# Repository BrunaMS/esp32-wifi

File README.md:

# esp32-wifi
In this project I'm using ESP32 with ESP-IDF framework to implement an Wi-Fi connection, allowing to download 500kb files from a device at least 100m away

## Firmware
### Environment
To develop and build this firmware I'm using VSCode and it's extensions. The main extension required to build it is platformIO but others like git extension can be used to help with version control and gitflow. 

### Task routine
To work with different services/threads I chose to use the  

## Hardware
For now, I'm using KiCad 6.0 to create schematics and PCB for this project. During the development was necessary to download components from external sources. These are:
- Example I
- Example II

### Components 
For this project some circuits are necessary, mainly to guarantee battery charging and to protect other modules and the microcontroller from damages.
- BQ - Battery control
- USB Protection circuit
- Crystal
- Voltage regulator
- Wi-Fi antenna performance
- GPIOs

### Microcontroller
The chosen microcontroller for this application was the ESP32-WROOM, developed to work with IoT and wireless in general, making wireless communication protocols easier to develop and use.

### Routing
The general rules for the routing process were:
1. Consider one manufacturer to define the correct pcb specifications (hole size, clearance, board thickness, impedance control, etc)
2. Always consider grounding rules
3. Avoid interference from power lines
4. Avoid keep high-speed signals close to other signals

## TODO 

|Area | Type |Description|
|-----|------|-----------|
|Firmware|Feature|Move device mode selector from kconfig to serial/nvs memory
|Firmware|Feature|Develop some type of interface to be used when it is in receiver mode
|Firmware|Fix| Convert components into real components (submodules in git), making possible the use in other projects
|Firmware|Fix| Organize the different "layers" of the project (e.g. components, common, task, main), creating uncoupled classes/libraries/functions
|Firmware|Docs| Explain function in header (.h file) of each component(brief, params, return) using Doxygen 
|Hardware|Test|Check if with built-in antenna can reach 100m of distance between devices or if its necessary to use another one |

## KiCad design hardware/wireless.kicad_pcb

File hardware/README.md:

# esp32-wifi
In this project I'm using ESP32 with PlatformIO framework to implement an Wi-Fi connection, allowing to download 100mb files from a device at least 100m away

## Firmware
### Environment
To develop and build this firmware I'm using VSCode and it's extensions. The main extension required to build it is platformIO but others like git extension can be used to help with version control and gitflow. 

### Task routine
To work with different services/threads I chose to use the  

## Hardware
For now, I'm using KiCad 6.0 to create schematics and PCB for this project. During the development was necessary to download components from external sources. These are:
- Example I
- Example II

### Components 
For this project some circuits are necessary, mainly to guarantee battery charging and to protect other modules and the microcontroller from damages.
- BQ
- USB Protection circuit
- Crystal
- Voltage regulator

### Microcontroller
The chosen microcontroller for this application was the ESP32-WROOM, developed to work with IoT and wireless in general, making wireless communication protocols easier to develop and use.

### Routing
The general rules for the routing process were:
1. Consider one manufacturer to define the correct pcb specifications (hole size, clearance, board thickness, impedance control, etc)
2. Always consider grounding rules
3. Avoid interference from power lines
4. Avoid keep high-speed signals close to other signals

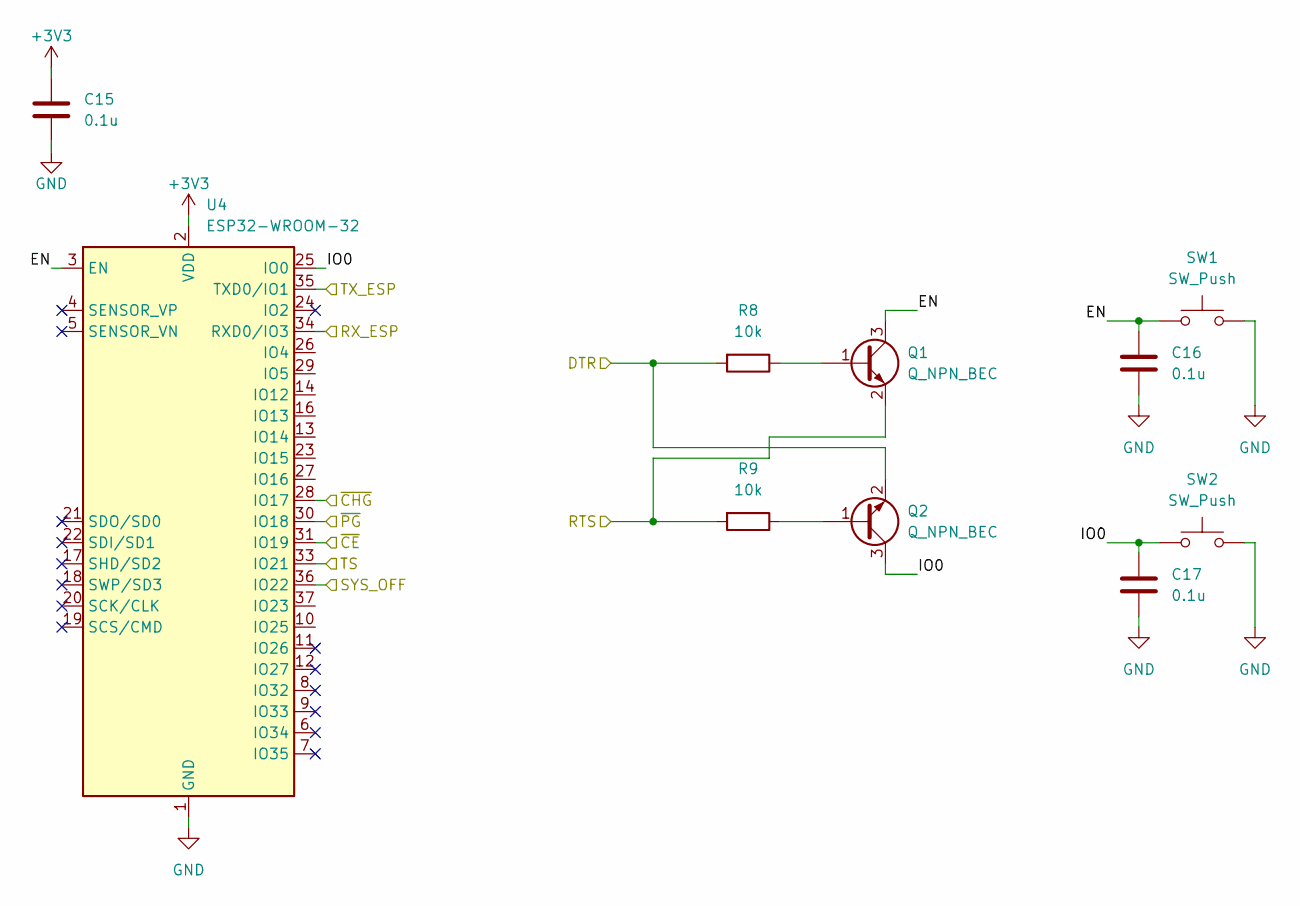
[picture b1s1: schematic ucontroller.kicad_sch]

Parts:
C15, C16, C17: 0.1u; C_0402_1005Metric
Q1, Q2: Q_NPN_BEC; SOT-323_SC-70
R8, R9: 10k; R_0402_1005Metric
SW1, SW2: SW_Push; SW_SPST_B3S-1000
U4: ESP32-WROOM-32

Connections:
+3V3: C15.1, U4.2 (VDD); also elsewhere on the board
/power_supply/SYS_OFF: U4.36 (IO22); also elsewhere on the board
/power_supply/TS: U4.33 (IO21); also elsewhere on the board
/power_supply/~CE: U4.31 (IO19); also elsewhere on the board
/power_supply/~CHG: U4.28 (IO17); also elsewhere on the board
/power_supply/~PG: U4.30 (IO18); also elsewhere on the board
/ucontroller/DTR: Q2.2 (E), R8.2; also elsewhere on the board
/ucontroller/EN: C16.1, Q1.3 (C), SW1.1, U4.3 (EN)
/ucontroller/IO0: C17.1, Q2.3 (C), SW2.1, U4.25 (IO0)
/ucontroller/RTS: Q1.2 (E), R9.2; also elsewhere on the board
/ucontroller/RX_ESP: U4.34 (RXD0/IO3); also elsewhere on the board
/ucontroller/TX_ESP: U4.35 (TXD0/IO1); also elsewhere on the board
GND: C15.2, C16.2, C17.2, SW1.2, SW2.2, U4.1 (GND), U4.15 (GND), U4.38 (GND), U4.39 (GND); also elsewhere on the board
unnamed: Q1.1 (B), R8.1
unnamed: Q2.1 (B), R9.1

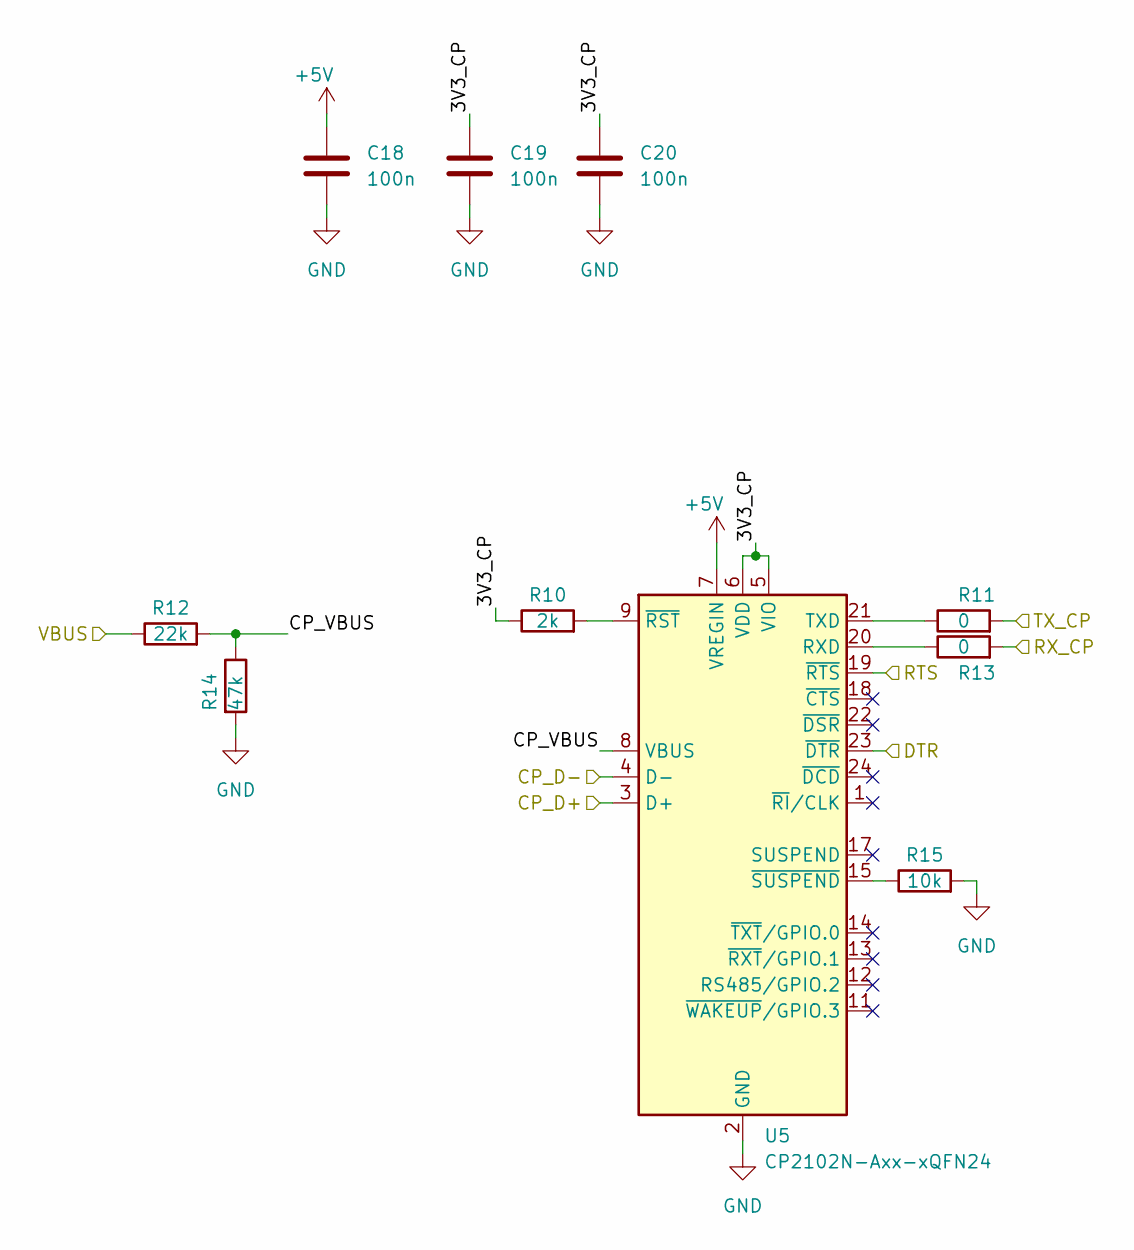
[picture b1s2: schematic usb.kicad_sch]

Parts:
C18, C19, C20: 100n; C_0402_1005Metric
R10: 2k; R_0402_1005Metric
R11, R13: 0; R_0402_1005Metric
R12: 22k; R_0402_1005Metric
R14: 47k; R_0402_1005Metric
R15: 10k; R_0402_1005Metric
U5: CP2102N-Axx-xQFN24; QFN-24-1EP_4x4mm_P0.5mm_EP2.6x2.6mm

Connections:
+5V: C18.1, R12.1, U5.7 (VREGIN); also elsewhere on the board
/power_supply/USB_D+: U5.3 (D+); also elsewhere on the board
/power_supply/USB_D-: U5.4 (D-); also elsewhere on the board
/ucontroller/DTR: U5.23 (~DTR); also elsewhere on the board
/ucontroller/RTS: U5.19 (~RTS); also elsewhere on the board
/ucontroller/RX_ESP: R11.2; also elsewhere on the board
/ucontroller/TX_ESP: R13.2; also elsewhere on the board
/usb/3V3_CP: C19.1, C20.1, R10.1, U5.5 (VIO), U5.6 (VDD)
/usb/CP_VBUS: R12.2, R14.1, U5.8 (VBUS)
GND: C18.2, C19.2, C20.2, R14.2, R15.2, U5.2 (GND), U5.25 (GND); also elsewhere on the board
unnamed: R10.2, U5.9 (~RST)
unnamed: R11.1, U5.21 (TXD)
unnamed: R13.1, U5.20 (RXD)
unnamed: R15.1, U5.15 (~SUSPEND)

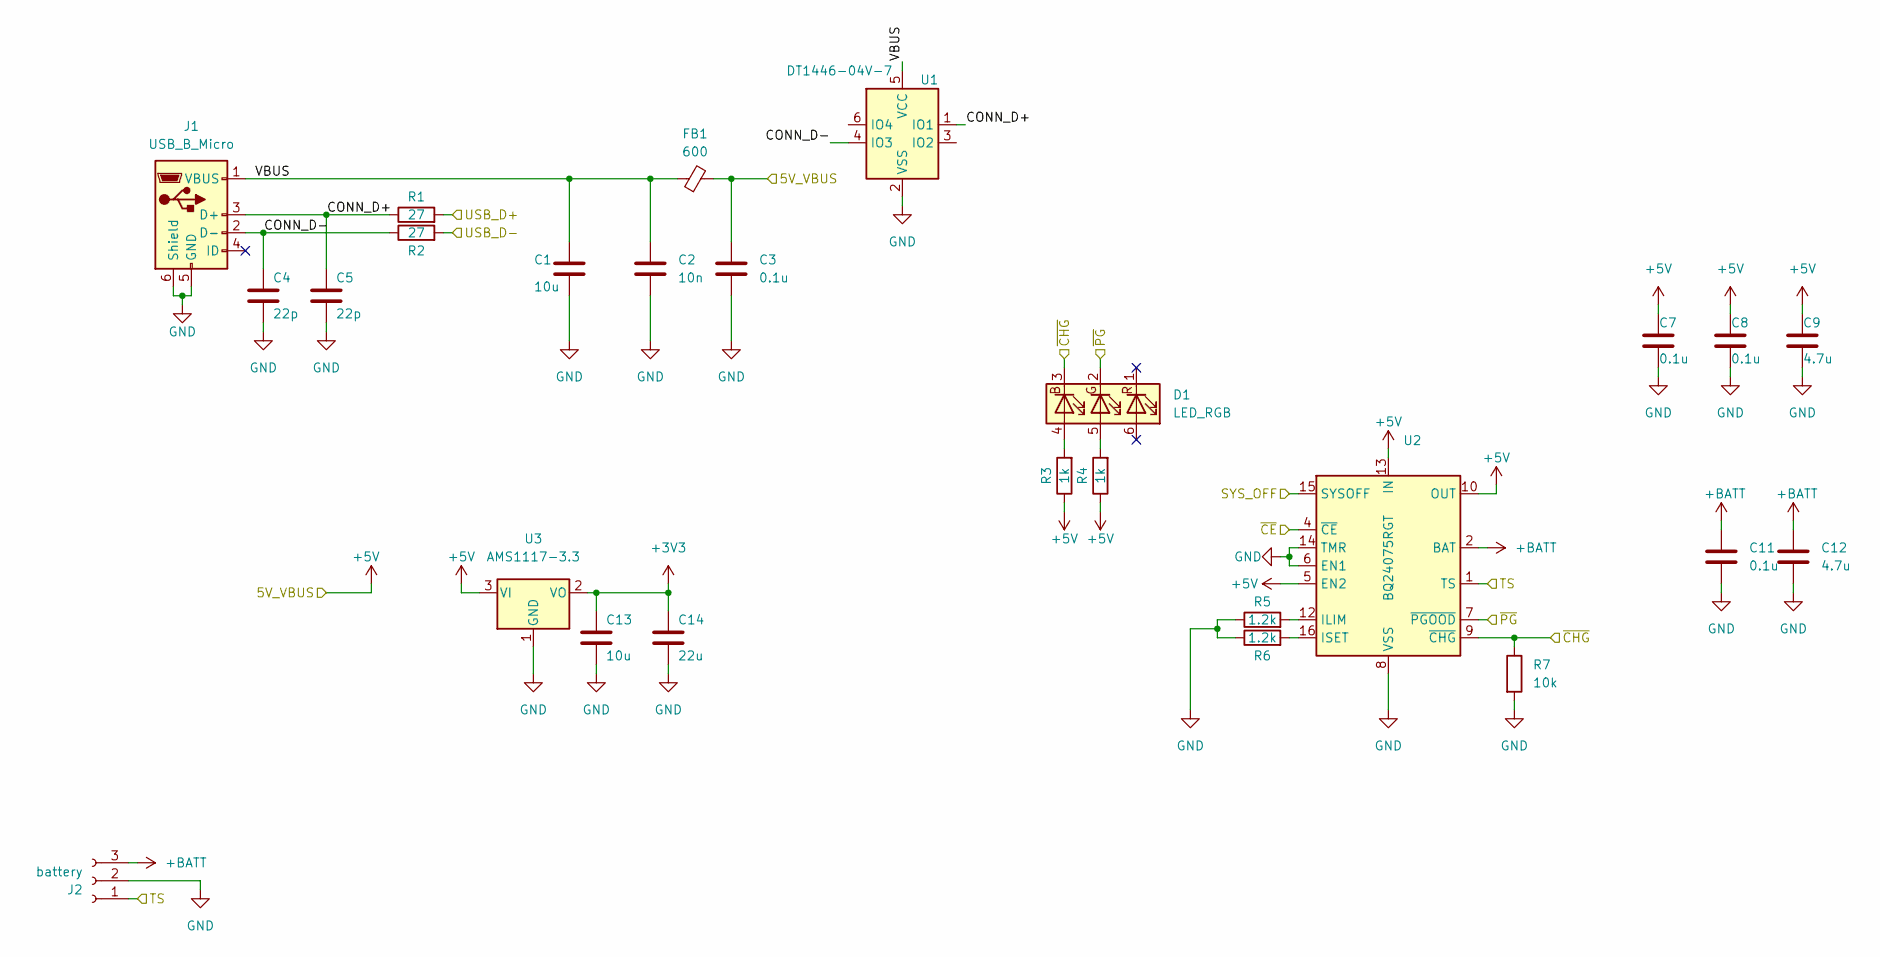
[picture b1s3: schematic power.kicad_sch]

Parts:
C1, C13: 10u; C_0603_1608Metric
C2: 10n; C_0402_1005Metric
C3, C7, C8, C11: 0.1u; C_0402_1005Metric
C4, C5: 22p; C_0402_1005Metric
C9, C12: 4.7u; C_0603_1608Metric
C14: 22u; C_0603_1608Metric
D1: LED_RGB; LED_RGB_5050-6
FB1: 600; L_0603_1608Metric
J1: USB_B_Micro; USB_Micro-B_Amphenol_10103594-0001LF_Horizontal
J2: battery; FanPinHeader_1x03_P2.54mm_Vertical
R1, R2: 27; R_0603_1608Metric
R3, R4: 1k; R_0402_1005Metric
R5, R6: 1.2k; R_0402_1005Metric
R7: 10k; R_0402_1005Metric
U1: DT1446-04V-7; SOT95P280X120-6N
U2: BQ24075RGT; VQFN-16-1EP_3x3mm_P0.5mm_EP1.6x1.6mm
U3: AMS1117-3.3; SOT-223-3_TabPin2

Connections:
+3V3: C13.1, C14.1, U3.2 (VO); also elsewhere on the board
+5V: C3.1, C7.1, C8.1, C9.1, FB1.2, R3.1, R4.1, U2.5 (EN2), U2.10 (OUT), U2.11 (OUT), U2.13 (IN), U3.3 (VI); also elsewhere on the board
+BATT: C11.1, C12.1, J2.3, U2.2 (BAT), U2.3 (BAT)
/power_supply/CONN_D+: C5.1, J1.3 (D+), R1.1, U1.1 (IO1)
/power_supply/CONN_D-: C4.1, J1.2 (D-), R2.1, U1.4 (IO3)
/power_supply/SYS_OFF: U2.15 (SYSOFF); also elsewhere on the board
/power_supply/TS: J2.1, U2.1 (TS); also elsewhere on the board
/power_supply/USB_D+: R1.2; also elsewhere on the board
/power_supply/USB_D-: R2.2; also elsewhere on the board
/power_supply/VBUS: C1.1, C2.1, FB1.1, J1.1 (VBUS), U1.5 (VCC)
/power_supply/~CE: U2.4 (~CE); also elsewhere on the board
/power_supply/~CHG: D1.3 (BK), R7.1, U2.9 (~CHG); also elsewhere on the board
/power_supply/~PG: D1.2 (GK), U2.7 (~PGOOD); also elsewhere on the board
GND: C1.2, C2.2, C3.2, C4.2, C5.2, C7.2, C8.2, C9.2, C11.2, C12.2, C13.2, C14.2, J1.5 (GND), J1.6 (Shield), J2.2, R5.1, R6.1, R7.2, U1.2 (VSS), U2.6 (EN1), U2.8 (VSS), U2.14 (TMR), U2.17 (VSS), U3.1 (GND); also elsewhere on the board
unnamed: D1.4 (BA), R3.2
unnamed: D1.5 (GA), R4.2
unnamed: R5.2, U2.12 (ILIM)
unnamed: R6.2, U2.16 (ISET)

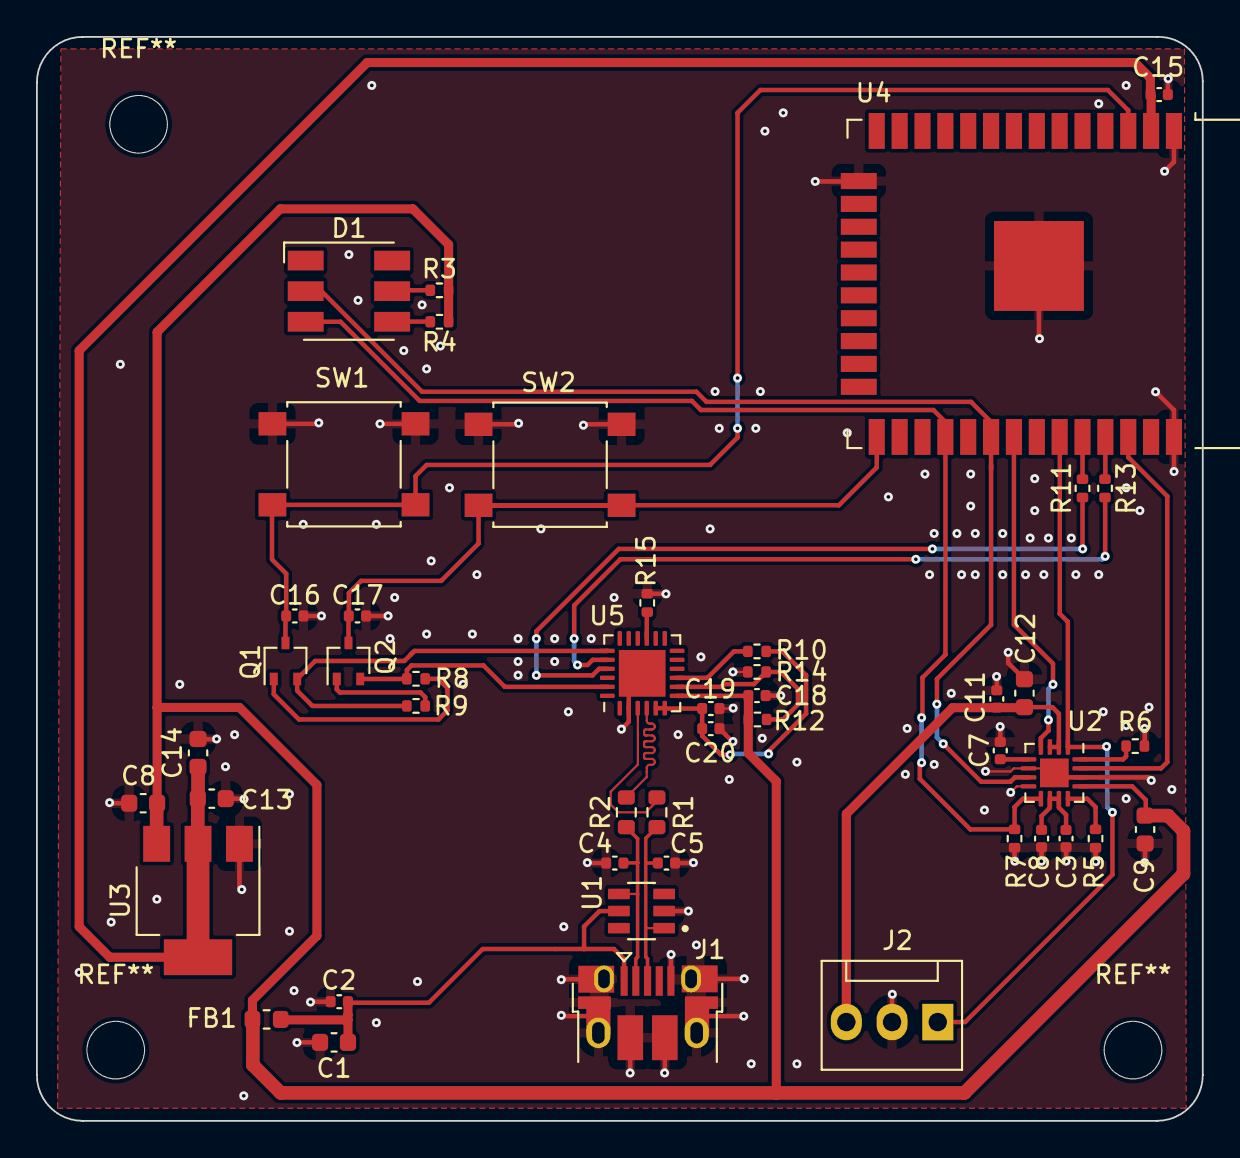
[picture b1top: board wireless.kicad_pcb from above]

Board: 2 copper layers, 64.8 x 60.2 mm, 47 parts (0 on the bottom side), 32 nets.

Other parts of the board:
C8#2: 0.1u; C_0402_1005Metric

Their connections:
+5V: C8#2.1; also elsewhere on the board
GND: C8#2.2; also elsewhere on the board

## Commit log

2022-09-13 Update README.md
    Create a documentation template to be follow.
2022-09-23 Create receiver module firmware
2022-09-29 Update project
    Modify kconfig according to project requirements
    Create 2 different modes (choose using kconfig): transmitter and receiver
    Start fs component development
    change project paths structure
2022-09-29 Create wifi transmitter module
2022-09-29 Update Read me
2022-09-29 Fix another error on receiver module (this time on wifi handler definitions)
2022-09-29 Fix errors using receiver mode
2022-09-29 Edit gitignore
2022-09-29 Implements filesystem
2022-09-29 Send file content using http and create table partition for spiffs usage
2022-09-30 Create httpClient
2022-10-02 Add scripts to test client and server
2022-10-03 Start hardware development
2022-10-04 finish hw development and generate gerber files
2022-10-04 return readme to the main path
